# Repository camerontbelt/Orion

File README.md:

## A simple, portable USB power supply

The Orion is a simple power module to convert a USB power source into a regulated positive and negative power supply for use with breadboards. It is designed to be small, and easily used with any five volt USB power brick. 

### What you will need
* USB B Mini cable
* 5V USB power brick

### Uses
* Opamps
* BJT circuits
* MOSFET circuits
* Any circuit you need a quick +/- voltage supply!

<a href="https://oshpark.com/shared_projects/w7GN6KGi"></img></a>

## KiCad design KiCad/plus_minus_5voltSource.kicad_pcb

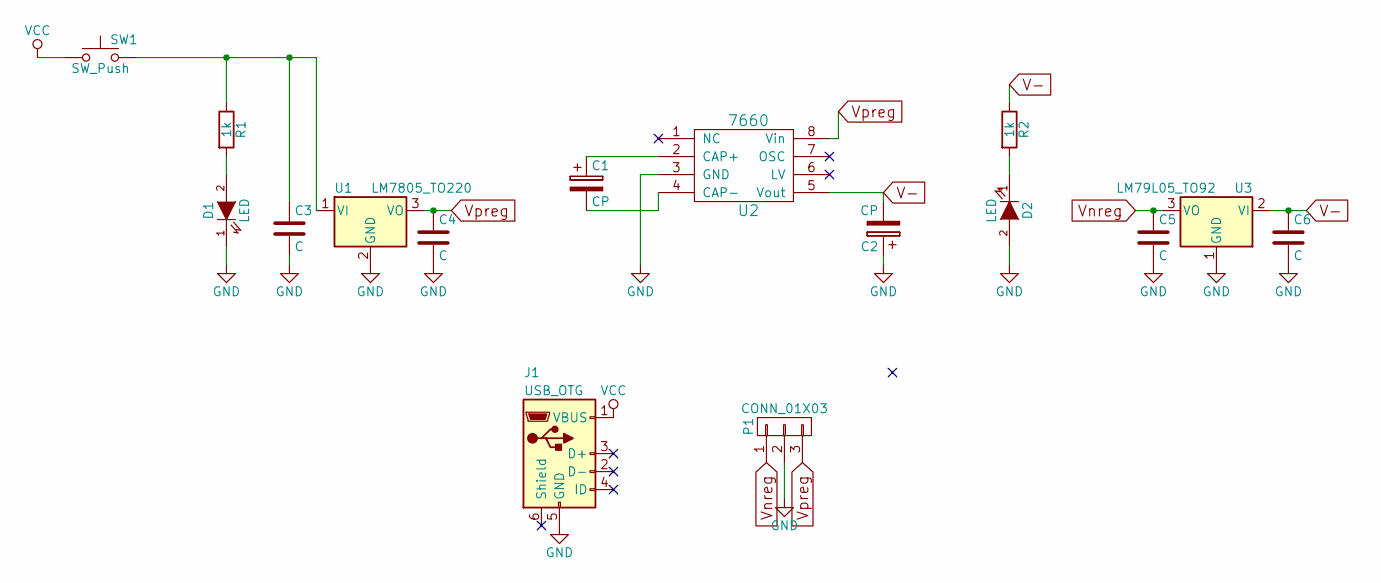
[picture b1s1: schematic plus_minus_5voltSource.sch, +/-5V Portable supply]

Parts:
C1, C2: CP; CP_Radial_D5.0mm_P2.50mm
C3, C4, C5, C6: C; C_Disc_D3.0mm_W2.0mm_P2.50mm
D1, D2: LED; LED_D3.0mm
J1: USB_OTG; USB_Micro-B
P1: CONN_01X03; Pin_Header_Angled_1x03_Pitch2.54mm
R1, R2: 1k; R_Axial_DIN0204_L3.6mm_D1.6mm_P5.08mm_Vertical
SW1: SW_Push; SW_PUSH_6mm
U1: LM7805_TO220; TO-92_Inline_Narrow_Oval
U2: 7660; DIP-8_W7.62mm
U3: LM79L05_TO92; TO-92_Inline_Narrow_Oval

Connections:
GND: C2.1, C3.2, C4.2, C5.2, C6.2, D1.1 (K), D2.2 (A), J1.5 (GND), P1.2, U1.2 (GND), U2.3 (GND), U3.1 (GND)
unnamed: C1.1, U2.2 (CAP+)
unnamed: C1.2, U2.4 (CAP-)
unnamed: C3.1, R1.1, SW1.2, U1.1 (VI)
unnamed: D1.2 (A), R1.2
unnamed: D2.1 (K), R2.2
V-: C2.2, C6.1, R2.1, U2.5 (Vout), U3.2 (VI)
VCC: J1.1 (VBUS), SW1.1
Vnreg: C5.1, P1.1, U3.3 (VO)
Vpreg: C4.1, P1.3, U1.3 (VO), U2.8 (Vin)

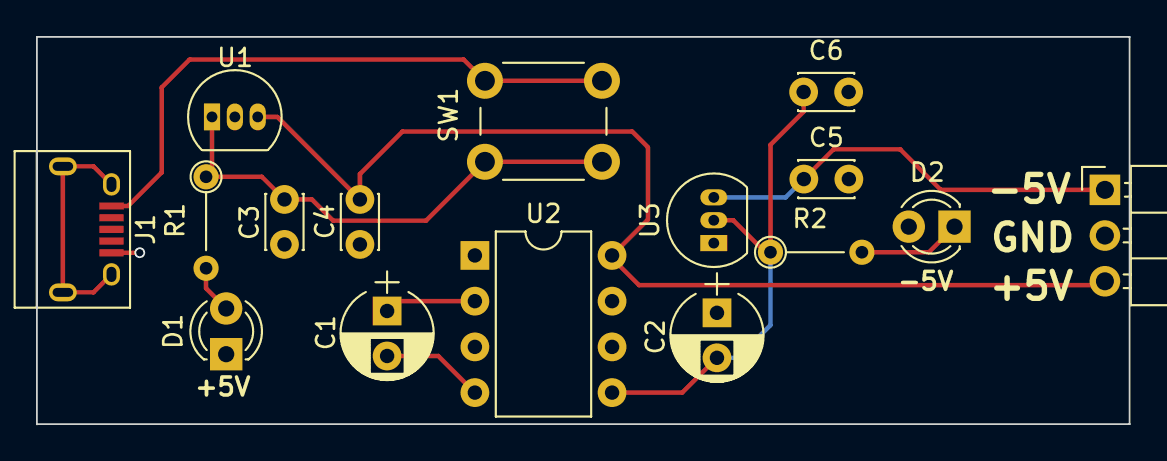
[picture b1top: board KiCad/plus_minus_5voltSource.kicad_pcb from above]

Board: 2 copper layers, 60.7 x 21.5 mm, 17 parts (1 on the bottom side), 10 nets.

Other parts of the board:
logo: logo

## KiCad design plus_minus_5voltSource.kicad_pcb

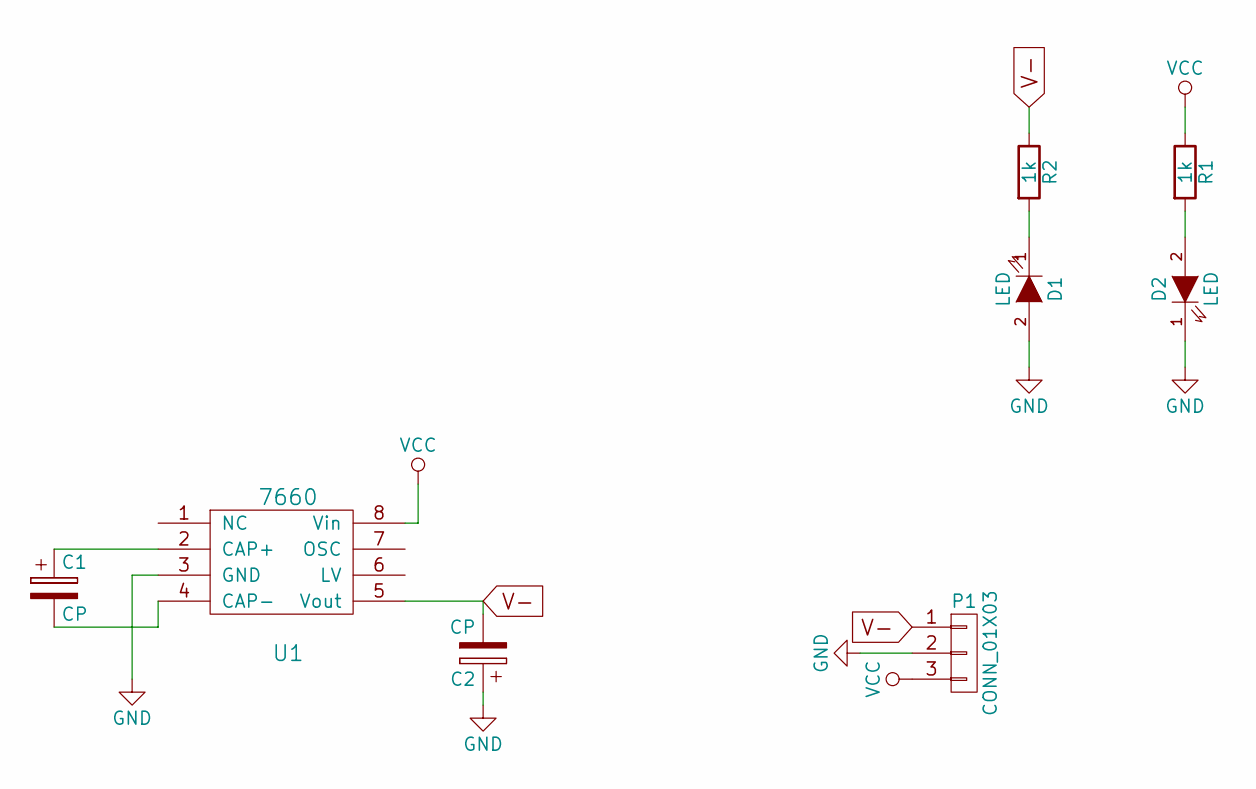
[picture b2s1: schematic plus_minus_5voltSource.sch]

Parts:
C1, C2: CP; C_Radial_D5_L6_P2.5
D1, D2: LED; LED_0805
P1: CONN_01X03; Pin_Header_Angled_1x03
R1, R2: 1k; R_0805_HandSoldering
U1: 7660; DIP-8_W7.62mm

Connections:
GND: C2.1, D1.2 (A), D2.1 (K), P1.2, U1.3 (GND)
unnamed: C1.1, U1.2 (CAP+)
unnamed: C1.2, U1.4 (CAP-)
unnamed: D1.1 (K), R2.2
unnamed: D2.2 (A), R1.2
V-: C2.2, P1.1, R2.1, U1.5 (Vout)
VCC: P1.3, R1.1, U1.8 (Vin)

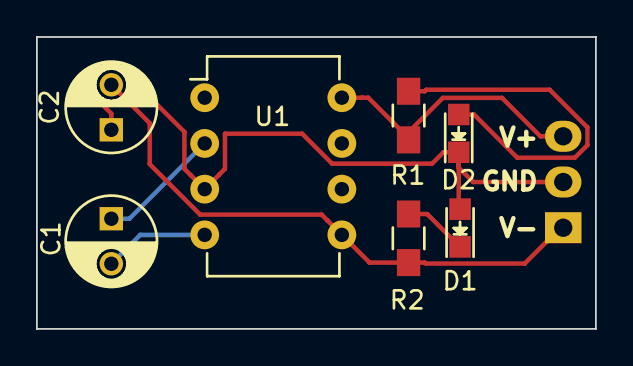
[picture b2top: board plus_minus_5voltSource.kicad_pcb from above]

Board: 2 copper layers, 31.1 x 16.2 mm, 8 parts (1 on the bottom side), 7 nets.

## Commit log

2017-12-12 Refactored schematic
2017-12-12 redesigned to have indicator leds, and voltage regulators
2017-12-12 added capacitors to voltage regulator lines.
2017-12-12 Added README.md file to repo.
2017-12-12 Added a heading to the README.
2017-12-12 Edited README.md to have more information.
2017-12-12 Added "made with kicad" to end of README.md
2017-12-12 Swapped out text with a badge.
2017-12-12 Fixed markdown for badge rendering.
2017-12-12 Changed folder structure to reflect a more organized and standardized approach for electronics projects from now forward. * Board Images - contains rendered or real images of the board * BoM - contai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
2017-12-12 Added open source badge to README.md
2017-12-13 Removed old PCB layout from the pcb file.
2017-12-13 Removed old board images and added a new, blank bom text file. This will be used to add components in the future.
2017-12-13 Changed some grammar in the README.md file.
2017-12-13 Finalized schematic by adding the usb connector for power and ground.
2017-12-13 Added bom information, create netlist, and associated footprints with symbols.
2017-12-13 Added pcb file to project.
2017-12-13 Edited component association to be all through hole components.
2017-12-13 Edited BoM to have updated part numbers
2017-12-14 Formatted BOM.
2017-12-14 Finalized pcb by adding edge cut, and routing to pcb.
2017-12-15 Added logo to PCB. Generated gerbers, and board images. Changed name of board to Orion.
2017-12-15 Changed name of board to Orion in README.md
2017-12-15 Edited voltage regulator part numbers to reflect actual part numbers. Added a schmatic folder with schematic pdf.
2017-12-15 Rotated board images 90 degrees.
2017-12-16 Added all components to the BoM.
2017-12-16 Changed schematic to reflect correct +5V regulator part number. Saved new PDF schematic sheet. Edited bom to have correct regulator digikey part number.
2017-12-16 Added OSHPark link to README.md.
2017-12-16 Deleted OSHPark title from above the link to the project.
2017-12-16 Replaced semi-colons with commas.
2017-12-17 Changed formatting of BoM to tabbed delimted text.
